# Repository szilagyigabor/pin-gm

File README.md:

# pin-gm
PIN-dióda alapú Geiger Müller-számláló

Hackaday összefoglaló: https://hackaday.com/2014/10/25/use-a-cheap-pin-diode-as-a-geiger-counter/
Német oldal többek között ennek a GM-számlálónak a részletes leírásával: http://opengeiger.de/index_en.html

BOM (a through hole schematic alapján, de főleg smd alkatrészekkel, 4 diódával):
	- BPW34, 4 db (az érzékelő PIN fotodióda) ok
	- TL 072CD, 1 db (valami smd változat) ok
	- LM358, 1 db (elvileg felületszerelt) ok
	- Jack, 1 db (S6BB 3.5mm mono szigetelt forrfüles Jack aljzat) ok
	- 9V elem csati, 1 db ok
	- 47 uF, 2 db (SMD, 1206 méret) ok
	- 100 nF, 7 db (SMD, 1206 méret) ok
	- 10 pF, 3 db (SMD, 1206 méret, visszacsatolásokhoz) ok
	- 10-40 pF trimmer, 1 db (through hole, d=10 mm, ?-200 pF helyett) ok
	- 4.7 Ohm, 1 db (SMD, 1206 méret) ok
	- 47 Ohm, 1 db (SMD, 1206 méret) ok
	- 1 kOhm, 5 db (SMD, 1206 méret) ok
	- 5.1 kOhm, 3 db (SMD, 1206 méret, 4.1 kOhm helyett) ok
	- 4.7 kOhm trimmer, 1 db (5 kOhm helyett) ok
	- 10 kOhm, 2 db (SMD, 1206 méret) ok
	- 15 kOhm, 1 db (SMD, 1206 méret) ok
	- 100 kOhm, 1 db (SMD, 1206 méret) ok
	- 10 MOhm, 1 db (SMD, 1206 méret) ok
	- 1 mH, 1 db (SMD-SRR0604) ok
	- doboz (75\*115.5\*54.5 mm, alu)
	- elem

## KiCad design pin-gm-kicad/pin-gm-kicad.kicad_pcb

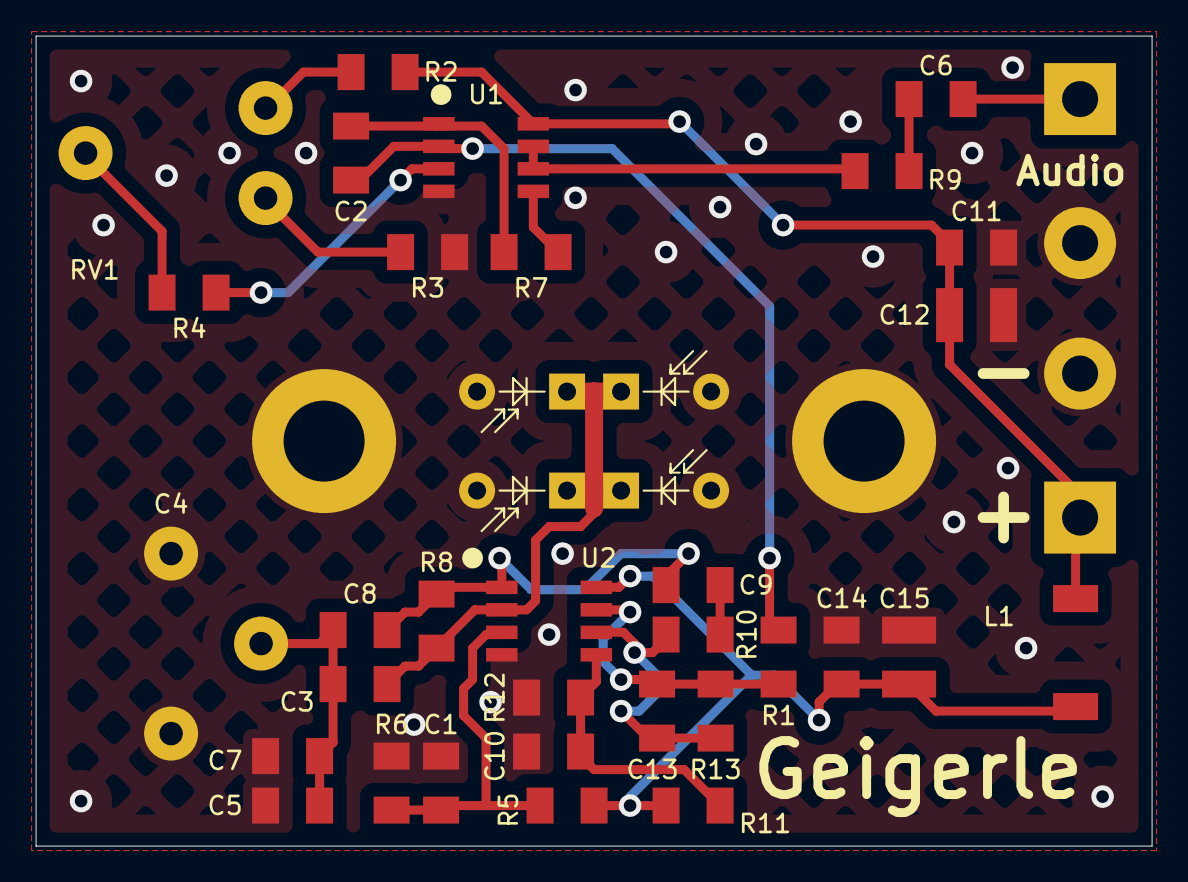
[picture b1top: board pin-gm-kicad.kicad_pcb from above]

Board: 2 copper layers, 62.0 x 45.0 mm, 40 parts (0 on the bottom side), 21 nets.

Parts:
BT1: Battery; SolderWire-homemade
C1, C2, C6, C9, C10, C11, C14: 100n; C_1206_3216Metric_homemade
C3, C5, C7, C8, C13: 10p; C_1206_3216Metric_homemade
C4: 10-40p; C_trimmer_D10mm_homemade
C12, C15: 47u; C_1210_3225Metric_homemade
D1, D2, D3, D4: BPW34; BPW34_homemade
H1, H2: MountingHole_Pad; Mounting_Hole_Dhole4mm_homemade
L1: 1m; L_Bourns_SRR0604_homemade
LS1: Speaker; SolderWire-homemade
R1, R4, R7, R9, R10: 1k; R_1206_3216Metric_homemade
R2, R3: 5k1; R_1206_3216Metric_homemade
R5: 4.7k; R_1206_3216Metric_homemade
R6: 15k; R_1206_3216Metric_homemade
R8: 10M; R_1206_3216Metric_homemade
R11, R12: 10k; R_1206_3216Metric_homemade
R13: 100k; R_1206_3216Metric_homemade
RV1: 5k; Potentiometer_D10_vert_homemade
U1: LM358; SO-8_3.9x4.9mm_homemade
U2: TL072; SO-8_3.9x4.9mm_homemade

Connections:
/Diode_Cathode: C3.1, D1.1 (K), D2.1 (K), D3.1 (K), D4.1 (K), R8.1, U2.2 (-)
GND: BT1.2 (-), C1.2, C4.2, C5.2, C7.2, C10.2, C11.2, C12.2, C14.2, C15.2, D1.2 (A), D2.2 (A), D3.2 (A), D4.2 (A), H1.1, H2.1, LS1.2, R3.2, R6.2, R12.2, U1.4 (V-), U2.4 (V-)
unnamed: C1.1, R5.2, R6.1, U2.3 (+)
unnamed: C2.1, R1.2, U1.2 (-)
unnamed: C2.2, R7.1, U1.1
unnamed: C3.2, C4.1, C5.1, C7.1, C8.1
unnamed: C6.1, R9.2
unnamed: C6.2, LS1.1
unnamed: C8.2, C9.1, R8.2, U2.1
unnamed: C9.2, R10.1
unnamed: C10.1, R11.2, R12.1, U2.5 (+)
unnamed: C13.1, R10.2, R13.1, U2.6 (-)
unnamed: C13.2, R1.1, R13.2, U2.7
unnamed: C14.1, C15.1, L1.1, R5.1, R11.1, U2.8 (V+)
unnamed: R2.2, RV1.1
unnamed: R3.1, RV1.3
unnamed: R4.1, RV1.2
unnamed: R4.2, U1.3 (+)
unnamed: R7.2, U1.5 (+)
unnamed: R9.1, U1.6 (-), U1.7
VCC: BT1.1 (+), C11.1, C12.1, L1.2, R2.1, U1.8 (V+)

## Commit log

2022-04-18 alap readme és források
2022-04-23 sokminden
    Még az LM358 és a trimmer kondenzátor footprintje hiányzik a schematicból
2022-04-23 trimmer kondi footprint kezdemény
2022-04-24 kb semmi
2022-04-25 kész vannak a footprintek
2022-04-27 egyéni footprintek
2022-04-27 kezdetleges layout
2022-04-29 kis haladás
2022-04-29 kb elhelyezve
2022-04-29 kb kész a layout
2022-04-29 mostmár tuti jó a layout
2022-04-30 téglalap körvonal, gerberek
2022-04-30 semmi
2022-05-07 forrasztási segédlet
